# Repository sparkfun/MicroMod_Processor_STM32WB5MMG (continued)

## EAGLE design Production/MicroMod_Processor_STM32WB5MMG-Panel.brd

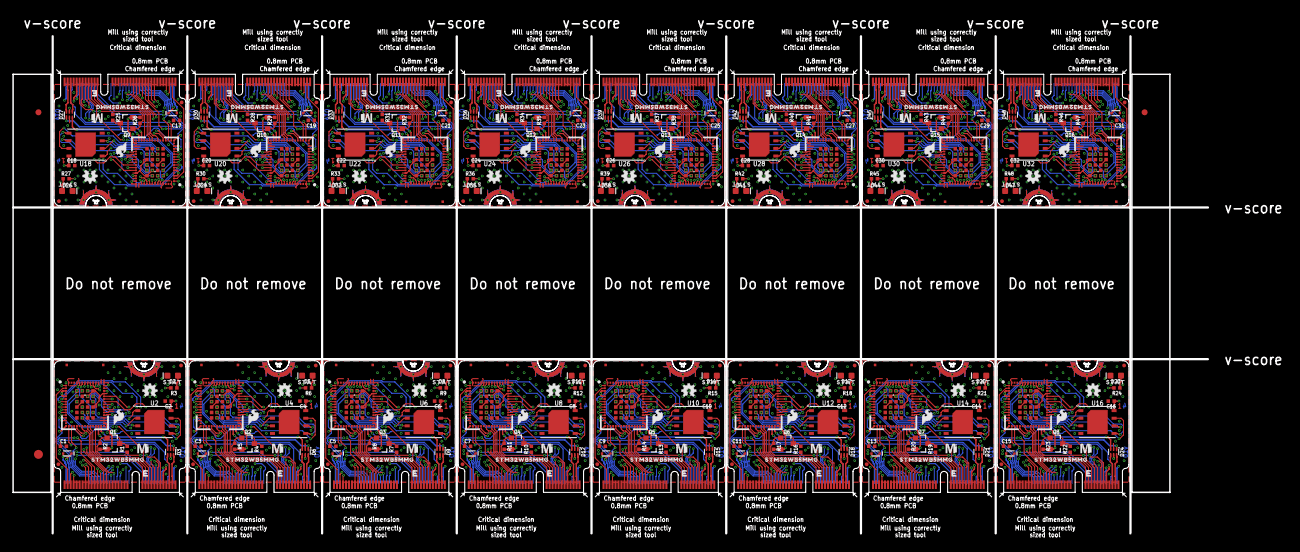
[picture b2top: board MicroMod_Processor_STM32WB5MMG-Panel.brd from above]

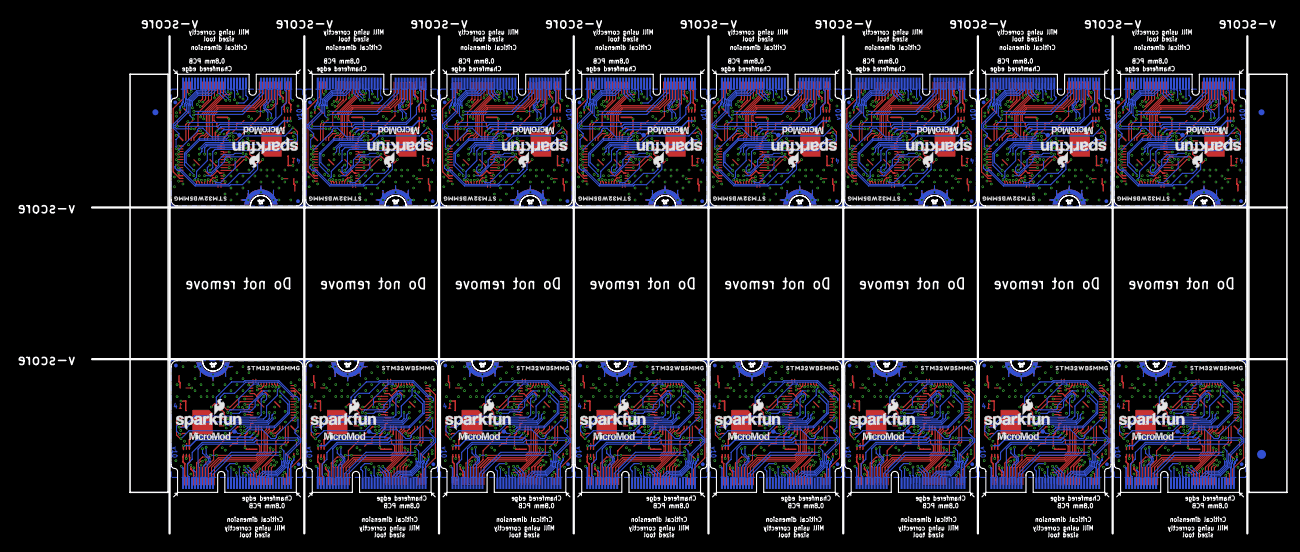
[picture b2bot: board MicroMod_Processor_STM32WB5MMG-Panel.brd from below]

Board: 4 copper layers, 199.6 x 83.1 mm, 438 parts (115 on the bottom side), 896 nets.

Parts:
C1, C2, C3, C4, C5, C6, C7, C8, C9, C10, C11, C12, C13, C14, C15, C16, C17, C18, C19, C20, C21, C22, C23, C24, C25, C26, C27, C28, C29, C30, C31, C32: 0.1uF; 0402-TIGHT
D1, D4, D7, D10, D13, D16, D19, D22, D25, D28, D31, D34, D37, D40, D43, D46: 120mA/40V/370mV; SOD-523
D2, D5, D8, D11, D14, D17, D20, D23, D26, D29, D32, D35, D38, D41, D44, D47: BLUE; LED-0603
D3, D6, D9, D12, D15, D18, D21, D24, D27, D30, D33, D36, D39, D42, D45, D48: PRTR5V0U2F; SOT886
E$1, E$2, E$3, E$4: FIDUCIAL-1X2
E$5, E$6: FIDUCIAL-1.5X3
FD1, FD2, FD3, FD4, FD5, FD6, FD7, FD8, FD9, FD10, FD11, FD12, FD13, FD14, FD15, FD16, FD17, FD18, FD19, FD20, FD21, FD22, FD23, FD24, FD25, FD26, FD27, FD28, FD29, FD30, FD31, FD32, FD33, FD34, FD35, FD36, FD37, FD38, FD39, FD40, FD41, FD42, FD43, FD44, FD45, FD46, FD47, FD48, FD49, FD50, FD51, FD52, FD53, FD54, FD55, FD56, FD57, FD58, FD59, FD60, FD61, FD62, FD63, FD64: FIDUCIALUFIDUCIAL; FIDUCIAL-MICRO
J1, J2, J3, J4, J5, J6, J7, J8, J9, J10, J11, J12, J13, J14, J15, J16: MICROMOD-2222; M.2-CARD-E-22
LOGO1, LOGO4, LOGO7, LOGO10, LOGO13, LOGO16, LOGO19, LOGO22, LOGO25, LOGO28, LOGO31, LOGO34, LOGO37, LOGO40, LOGO43, LOGO46: FOUR_LAYER_WARNING
LOGO2, LOGO5, LOGO8, LOGO11, LOGO14, LOGO17, LOGO20, LOGO23, LOGO26, LOGO29, LOGO32, LOGO35, LOGO38, LOGO41, LOGO44, LOGO47: OSHW-LOGOMINI; OSHW-LOGO-MINI
LOGO3, LOGO6, LOGO9, LOGO12, LOGO15, LOGO18, LOGO21, LOGO24, LOGO27, LOGO30, LOGO33, LOGO36, LOGO39, LOGO42, LOGO45, LOGO48: SFE_LOGO_NAME_FLAME.1_INCH; SFE_LOGO_NAME_FLAME_.1
Q1, Q2, Q3, Q4, Q5, Q6, Q7, Q8, Q9, Q10, Q11, Q12, Q13, Q14, Q15, Q16: 20V/4.2A/52mΩ/1.4W; SOT23-3
R1, R2, R4, R5, R7, R8, R10, R11, R13, R14, R16, R17, R19, R20, R22, R23, R25, R26, R28, R29, R31, R32, R34, R35, R37, R38, R40, R41, R43, R44, R46, R47: 100k; 0402-TIGHT
R3, R6, R9, R12, R15, R18, R21, R24, R27, R30, R33, R36, R39, R42, R45, R48: 2.2k; 0402-TIGHT
TP1, TP2, TP3, TP4, TP5, TP6, TP7, TP8, TP9, TP10, TP11, TP12, TP13, TP14, TP15, TP16: TEST-POINT3; PAD.03X.03
U1, U3, U5, U7, U9, U11, U13, U15, U17, U19, U21, U23, U25, U27, U29, U31: STM32WB5MMG; SIP-LGA86
U2, U4, U6, U8, U10, U12, U14, U16, U18, U20, U22, U24, U26, U28, U30, U32: W25QXX128MBIT-6X5; WSON-8-6X5
U$1, U$8, U$15, U$22, U$29, U$36, U$43, U$50, U$57, U$64, U$71, U$78, U$85, U$92, U$99, U$106: MICROMOD_MI_LOGO_.35
U$2, U$9, U$16, U$23, U$30, U$37, U$44, U$51, U$58, U$65, U$72, U$79, U$86, U$93, U$100, U$107: MICROMOD_LOGO_.3
U$3, U$10, U$17, U$24, U$31, U$38, U$45, U$52, U$59, U$66, U$73, U$80, U$87, U$94, U$101, U$108: SFE_LOGO_FLAME_.1
U$4, U$5, U$11, U$12, U$18, U$19, U$25, U$26, U$32, U$33, U$39, U$40, U$46, U$47, U$53, U$54, U$60, U$61, U$67, U$68, U$74, U$75, U$81, U$82, U$88, U$89, U$95, U$96, U$102, U$103, U$109, U$110: STM32WB5MMG0
U$6, U$13, U$20, U$27, U$34, U$41, U$48, U$55, U$62, U$69, U$76, U$83, U$90, U$97, U$104, U$111: SFE_LOGO_FLAME_STOP_.1
U$7, U$14, U$21, U$28, U$35, U$42, U$49, U$56, U$63, U$70, U$77, U$84, U$91, U$98, U$105, U$112: STAT0

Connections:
3.3V: C2.1, D1.A, J1.2, J1.74, Q1.2, R2.2, U1.4, U1.6, U1.17, U1.32, U2.8
3.3V1: C4.1, D4.A, J2.2, J2.74, Q2.2, R5.2, U3.4, U3.6, U3.17, U3.32, U4.8
3.3V2: C6.1, D7.A, J3.2, J3.74, Q3.2, R8.2, U5.4, U5.6, U5.17, U5.32, U6.8
3.3V3: C8.1, D10.A, J4.2, J4.74, Q4.2, R11.2, U7.4, U7.6, U7.17, U7.32, U8.8
3.3V4: C10.1, D13.A, J5.2, J5.74, Q5.2, R14.2, U9.4, U9.6, U9.17, U9.32, U10.8
3.3V5: C12.1, D16.A, J6.2, J6.74, Q6.2, R17.2, U11.4, U11.6, U11.17, U11.32, U12.8
3.3V6: C14.1, D19.A, J7.2, J7.74, Q7.2, R20.2, U13.4, U13.6, U13.17, U13.32, U14.8
3.3V7: C16.1, D22.A, J8.2, J8.74, Q8.2, R23.2, U15.4, U15.6, U15.17, U15.32, U16.8
3.3V8: C18.1, D25.A, J9.2, J9.74, Q9.2, R26.2, U17.4, U17.6, U17.17, U17.32, U18.8
3.3V9: C20.1, D28.A, J10.2, J10.74, Q10.2, R29.2, U19.4, U19.6, U19.17, U19.32, U20.8
3.3V10: C22.1, D31.A, J11.2, J11.74, Q11.2, R32.2, U21.4, U21.6, U21.17, U21.32, U22.8
3.3V11: C24.1, D34.A, J12.2, J12.74, Q12.2, R35.2, U23.4, U23.6, U23.17, U23.32, U24.8
3.3V12: C26.1, D37.A, J13.2, J13.74, Q13.2, R38.2, U25.4, U25.6, U25.17, U25.32, U26.8
3.3V13: C28.1, D40.A, J14.2, J14.74, Q14.2, R41.2, U27.4, U27.6, U27.17, U27.32, U28.8
3.3V14: C30.1, D43.A, J15.2, J15.74, Q15.2, R44.2, U29.4, U29.6, U29.17, U29.32, U30.8
3.3V15: C32.1, D46.A, J16.2, J16.74, Q16.2, R47.2, U31.4, U31.6, U31.17, U31.32, U32.8
!BOOT!: J1.11, Q1.1, R2.1
!BOOT!1: J2.11, Q2.1, R5.1
!BOOT!2: J3.11, Q3.1, R8.1
!BOOT!3: J4.11, Q4.1, R11.1
!BOOT!4: J5.11, Q5.1, R14.1
!BOOT!5: J6.11, Q6.1, R17.1
!BOOT!6: J7.11, Q7.1, R20.1
!BOOT!7: J8.11, Q8.1, R23.1
!BOOT!8: J9.11, Q9.1, R26.1
!BOOT!9: J10.11, Q10.1, R29.1
!BOOT!10: J11.11, Q11.1, R32.1
!BOOT!11: J12.11, Q12.1, R35.1
!BOOT!12: J13.11, Q13.1, R38.1
!BOOT!13: J14.11, Q14.1, R41.1
!BOOT!14: J15.11, Q15.1, R44.1
!BOOT!15: J16.11, Q16.1, R47.1
!RESET!: C1.1, J1.6, U1.10
!RESET!1: C3.1, J2.6, U3.10
!RESET!2: C5.1, J3.6, U5.10
!RESET!3: C7.1, J4.6, U7.10
!RESET!4: C9.1, J5.6, U9.10
!RESET!5: C11.1, J6.6, U11.10
!RESET!6: C13.1, J7.6, U13.10
!RESET!7: C15.1, J8.6, U15.10
!RESET!8: C17.1, J9.6, U17.10
!RESET!9: C19.1, J10.6, U19.10
!RESET!10: C21.1, J11.6, U21.10
!RESET!11: C23.1, J12.6, U23.10
!RESET!12: C25.1, J13.6, U25.10
!RESET!13: C27.1, J14.6, U27.10
!RESET!14: C29.1, J15.6, U29.10
!RESET!15: C31.1, J16.6, U31.10
A0: J1.34, U1.8
A1: J1.38, U1.7
A2: J2.34, U3.8
A3: J2.38, U3.7
A4: J3.34, U5.8
A5: J3.38, U5.7
A6: J4.34, U7.8
A7: J4.38, U7.7
A8: J5.34, U9.8
A9: J5.38, U9.7
A10: J6.34, U11.8
A11: J6.38, U11.7
A12: J7.34, U13.8
A13: J7.38, U13.7
A14: J8.34, U15.8
A15: J8.38, U15.7
A16: J9.34, U17.8
A17: J9.38, U17.7
A18: J10.34, U19.8
A19: J10.38, U19.7
A20: J11.34, U21.8
A21: J11.38, U21.7
A22: J12.34, U23.8
A23: J12.38, U23.7
A24: J13.34, U25.8
A25: J13.38, U25.7
A26: J14.34, U27.8
A27: J14.38, U27.7
A28: J15.34, U29.8
A29: J15.38, U29.7
A30: J16.34, U31.8
A31: J16.38, U31.7
AUD_BCLK: J1.50, U1.50
AUD_BCLK1: J2.50, U3.50
AUD_BCLK2: J3.50, U5.50
AUD_BCLK3: J4.50, U7.50
AUD_BCLK4: J5.50, U9.50
AUD_BCLK5: J6.50, U11.50
AUD_BCLK6: J7.50, U13.50
AUD_BCLK7: J8.50, U15.50
AUD_BCLK8: J9.50, U17.50
AUD_BCLK9: J10.50, U19.50
AUD_BCLK10: J11.50, U21.50
AUD_BCLK11: J12.50, U23.50
AUD_BCLK12: J13.50, U25.50
AUD_BCLK13: J14.50, U27.50
AUD_BCLK14: J15.50, U29.50
AUD_BCLK15: J16.50, U31.50
AUD_FSYNC: J1.52, U1.11
AUD_FSYNC1: J2.52, U3.11
AUD_FSYNC2: J3.52, U5.11
AUD_FSYNC3: J4.52, U7.11
AUD_FSYNC4: J5.52, U9.11
AUD_FSYNC5: J6.52, U11.11
AUD_FSYNC6: J7.52, U13.11
AUD_FSYNC7: J8.52, U15.11
AUD_FSYNC8: J9.52, U17.11
AUD_FSYNC9: J10.52, U19.11
AUD_FSYNC10: J11.52, U21.11
AUD_FSYNC11: J12.52, U23.11
AUD_FSYNC12: J13.52, U25.11
AUD_FSYNC13: J14.52, U27.11
AUD_FSYNC14: J15.52, U29.11
AUD_FSYNC15: J16.52, U31.11
AUD_I2S_IN: J1.54, U1.19
AUD_I2S_IN1: J2.54, U3.19
AUD_I2S_IN2: J3.54, U5.19
AUD_I2S_IN3: J4.54, U7.19
AUD_I2S_IN4: J5.54, U9.19
AUD_I2S_IN5: J6.54, U11.19
AUD_I2S_IN6: J7.54, U13.19
AUD_I2S_IN7: J8.54, U15.19
AUD_I2S_IN8: J9.54, U17.19
AUD_I2S_IN9: J10.54, U19.19
AUD_I2S_IN10: J11.54, U21.19
AUD_I2S_IN11: J12.54, U23.19
AUD_I2S_IN12: J13.54, U25.19
AUD_I2S_IN13: J14.54, U27.19
AUD_I2S_IN14: J15.54, U29.19
AUD_I2S_IN15: J16.54, U31.19
AUD_I2S_OUT: J1.56, U1.38
AUD_I2S_OUT1: J2.56, U3.38
AUD_I2S_OUT2: J3.56, U5.38
AUD_I2S_OUT3: J4.56, U7.38
AUD_I2S_OUT4: J5.56, U9.38
AUD_I2S_OUT5: J6.56, U11.38
AUD_I2S_OUT6: J7.56, U13.38
AUD_I2S_OUT7: J8.56, U15.38
AUD_I2S_OUT8: J9.56, U17.38
AUD_I2S_OUT9: J10.56, U19.38
AUD_I2S_OUT10: J11.56, U21.38
AUD_I2S_OUT11: J12.56, U23.38
AUD_I2S_OUT12: J13.56, U25.38
AUD_I2S_OUT13: J14.56, U27.38
AUD_I2S_OUT14: J15.56, U29.38
AUD_I2S_OUT15: J16.56, U31.38
AUD_MCLK: J1.58, U1.14
AUD_MCLK1: J2.58, U3.14
AUD_MCLK2: J3.58, U5.14
AUD_MCLK3: J4.58, U7.14
AUD_MCLK4: J5.58, U9.14
AUD_MCLK5: J6.58, U11.14
AUD_MCLK6: J7.58, U13.14
AUD_MCLK7: J8.58, U15.14
AUD_MCLK8: J9.58, U17.14
AUD_MCLK9: J10.58, U19.14
AUD_MCLK10: J11.58, U21.14
AUD_MCLK11: J12.58, U23.14
AUD_MCLK12: J13.58, U25.14
AUD_MCLK13: J14.58, U27.14
AUD_MCLK14: J15.58, U29.14
AUD_MCLK15: J16.58, U31.14
BATT_VIN: J1.49, U1.49
BATT_VIN1: J2.49, U3.49
BATT_VIN2: J3.49, U5.49
BATT_VIN3: J4.49, U7.49
BATT_VIN4: J5.49, U9.49
BATT_VIN5: J6.49, U11.49
BATT_VIN6: J7.49, U13.49
BATT_VIN7: J8.49, U15.49
BATT_VIN8: J9.49, U17.49
BATT_VIN9: J10.49, U19.49
BATT_VIN10: J11.49, U21.49
BATT_VIN11: J12.49, U23.49
BATT_VIN12: J13.49, U25.49
BATT_VIN13: J14.49, U27.49
BATT_VIN14: J15.49, U29.49
BATT_VIN15: J16.49, U31.49
BOOT0: Q1.3, R1.2, TP1.1, U1.13
BOOT1: Q2.3, R4.2, TP2.1, U3.13
BOOT2: Q3.3, R7.2, TP3.1, U5.13
BOOT3: Q4.3, R10.2, TP4.1, U7.13
BOOT4: Q5.3, R13.2, TP5.1, U9.13
BOOT5: Q6.3, R16.2, TP6.1, U11.13
BOOT6: Q7.3, R19.2, TP7.1, U13.13
BOOT7: Q8.3, R22.2, TP8.1, U15.13
BOOT8: Q9.3, R25.2, TP9.1, U17.13
BOOT9: Q10.3, R28.2, TP10.1, U19.13
BOOT10: Q11.3, R31.2, TP11.1, U21.13
BOOT11: Q12.3, R34.2, TP12.1, U23.13
BOOT12: Q13.3, R37.2, TP13.1, U25.13
BOOT13: Q14.3, R40.2, TP14.1, U27.13
BOOT14: Q15.3, R43.2, TP15.1, U29.13
BOOT15: Q16.3, R46.2, TP16.1, U31.13
GND: C1.2, C2.2, D2.C, D3.2, J1.1, J1.7, J1.33, J1.36, J1.39, J1.45, J1.75, J1.GND1, J1.GND2, J1.GND3, R1.1, U1.5, U1.16, U1.22, U1.24, U1.27, U1.31, U1.33, U1.34, U1.36, U1.43, U1.44, U1.45, U1.46, U1.47, U1.48, U1.57, U1.58, U1.59, U1.60, U1.64, U1.65, U1.66, U1.68, U1.69, U1.71, U1.74, U1.77, U1.78, U1.82, U1.83, U1.84, U1.86, U2.4
GND2: C3.2, C4.2, D5.C, D6.2, J2.1, J2.7, J2.33, J2.36, J2.39, J2.45, J2.75, J2.GND1, J2.GND2, J2.GND3, R4.1, U3.5, U3.16, U3.22, U3.24, U3.27, U3.31, U3.33, U3.34, U3.36, U3.43, U3.44, U3.45, U3.46, U3.47, U3.48, U3.57, U3.58, U3.59, U3.60, U3.64, U3.65, U3.66, U3.68, U3.69, U3.71, U3.74, U3.77, U3.78, U3.82, U3.83, U3.84, U3.86, U4.4
GND4: C5.2, C6.2, D8.C, D9.2, J3.1, J3.7, J3.33, J3.36, J3.39, J3.45, J3.75, J3.GND1, J3.GND2, J3.GND3, R7.1, U5.5, U5.16, U5.22, U5.24, U5.27, U5.31, U5.33, U5.34, U5.36, U5.43, U5.44, U5.45, U5.46, U5.47, U5.48, U5.57, U5.58, U5.59, U5.60, U5.64, U5.65, U5.66, U5.68, U5.69, U5.71, U5.74, U5.77, U5.78, U5.82, U5.83, U5.84, U5.86, U6.4
GND6: C7.2, C8.2, D11.C, D12.2, J4.1, J4.7, J4.33, J4.36, J4.39, J4.45, J4.75, J4.GND1, J4.GND2, J4.GND3, R10.1, U7.5, U7.16, U7.22, U7.24, U7.27, U7.31, U7.33, U7.34, U7.36, U7.43, U7.44, U7.45, U7.46, U7.47, U7.48, U7.57, U7.58, U7.59, U7.60, U7.64, U7.65, U7.66, U7.68, U7.69, U7.71, U7.74, U7.77, U7.78, U7.82, U7.83, U7.84, U7.86, U8.4
GND8: C9.2, C10.2, D14.C, D15.2, J5.1, J5.7, J5.33, J5.36, J5.39, J5.45, J5.75, J5.GND1, J5.GND2, J5.GND3, R13.1, U9.5, U9.16, U9.22, U9.24, U9.27, U9.31, U9.33, U9.34, U9.36, U9.43, U9.44, U9.45, U9.46, U9.47, U9.48, U9.57, U9.58, U9.59, U9.60, U9.64, U9.65, U9.66, U9.68, U9.69, U9.71, U9.74, U9.77, U9.78, U9.82, U9.83, U9.84, U9.86, U10.4
GND10: C11.2, C12.2, D17.C, D18.2, J6.1, J6.7, J6.33, J6.36, J6.39, J6.45, J6.75, J6.GND1, J6.GND2, J6.GND3, R16.1, U11.5, U11.16, U11.22, U11.24, U11.27, U11.31, U11.33, U11.34, U11.36, U11.43, U11.44, U11.45, U11.46, U11.47, U11.48, U11.57, U11.58, U11.59, U11.60, U11.64, U11.65, U11.66, U11.68, U11.69, U11.71, U11.74, U11.77, U11.78, U11.82, U11.83, U11.84, U11.86, U12.4
GND12: C13.2, C14.2, D20.C, D21.2, J7.1, J7.7, J7.33, J7.36, J7.39, J7.45, J7.75, J7.GND1, J7.GND2, J7.GND3, R19.1, U13.5, U13.16, U13.22, U13.24, U13.27, U13.31, U13.33, U13.34, U13.36, U13.43, U13.44, U13.45, U13.46, U13.47, U13.48, U13.57, U13.58, U13.59, U13.60, U13.64, U13.65, U13.66, U13.68, U13.69, U13.71, U13.74, U13.77, U13.78, U13.82, U13.83, U13.84, U13.86, U14.4
GND14: C15.2, C16.2, D23.C, D24.2, J8.1, J8.7, J8.33, J8.36, J8.39, J8.45, J8.75, J8.GND1, J8.GND2, J8.GND3, R22.1, U15.5, U15.16, U15.22, U15.24, U15.27, U15.31, U15.33, U15.34, U15.36, U15.43, U15.44, U15.45, U15.46, U15.47, U15.48, U15.57, U15.58, U15.59, U15.60, U15.64, U15.65, U15.66, U15.68, U15.69, U15.71, U15.74, U15.77, U15.78, U15.82, U15.83, U15.84, U15.86, U16.4
GND16: C17.2, C18.2, D26.C, D27.2, J9.1, J9.7, J9.33, J9.36, J9.39, J9.45, J9.75, J9.GND1, J9.GND2, J9.GND3, R25.1, U17.5, U17.16, U17.22, U17.24, U17.27, U17.31, U17.33, U17.34, U17.36, U17.43, U17.44, U17.45, U17.46, U17.47, U17.48, U17.57, U17.58, U17.59, U17.60, U17.64, U17.65, U17.66, U17.68, U17.69, U17.71, U17.74, U17.77, U17.78, U17.82, U17.83, U17.84, U17.86, U18.4
GND18: C19.2, C20.2, D29.C, D30.2, J10.1, J10.7, J10.33, J10.36, J10.39, J10.45, J10.75, J10.GND1, J10.GND2, J10.GND3, R28.1, U19.5, U19.16, U19.22, U19.24, U19.27, U19.31, U19.33, U19.34, U19.36, U19.43, U19.44, U19.45, U19.46, U19.47, U19.48, U19.57, U19.58, U19.59, U19.60, U19.64, U19.65, U19.66, U19.68, U19.69, U19.71, U19.74, U19.77, U19.78, U19.82, U19.83, U19.84, U19.86, U20.4
GND20: C21.2, C22.2, D32.C, D33.2, J11.1, J11.7, J11.33, J11.36, J11.39, J11.45, J11.75, J11.GND1, J11.GND2, J11.GND3, R31.1, U21.5, U21.16, U21.22, U21.24, U21.27, U21.31, U21.33, U21.34, U21.36, U21.43, U21.44, U21.45, U21.46, U21.47, U21.48, U21.57, U21.58, U21.59, U21.60, U21.64, U21.65, U21.66, U21.68, U21.69, U21.71, U21.74, U21.77, U21.78, U21.82, U21.83, U21.84, U21.86, U22.4
GND22: C23.2, C24.2, D35.C, D36.2, J12.1, J12.7, J12.33, J12.36, J12.39, J12.45, J12.75, J12.GND1, J12.GND2, J12.GND3, R34.1, U23.5, U23.16, U23.22, U23.24, U23.27, U23.31, U23.33, U23.34, U23.36, U23.43, U23.44, U23.45, U23.46, U23.47, U23.48, U23.57, U23.58, U23.59, U23.60, U23.64, U23.65, U23.66, U23.68, U23.69, U23.71, U23.74, U23.77, U23.78, U23.82, U23.83, U23.84, U23.86, U24.4
GND24: C25.2, C26.2, D38.C, D39.2, J13.1, J13.7, J13.33, J13.36, J13.39, J13.45, J13.75, J13.GND1, J13.GND2, J13.GND3, R37.1, U25.5, U25.16, U25.22, U25.24, U25.27, U25.31, U25.33, U25.34, U25.36, U25.43, U25.44, U25.45, U25.46, U25.47, U25.48, U25.57, U25.58, U25.59, U25.60, U25.64, U25.65, U25.66, U25.68, U25.69, U25.71, U25.74, U25.77, U25.78, U25.82, U25.83, U25.84, U25.86, U26.4
GND26: C27.2, C28.2, D41.C, D42.2, J14.1, J14.7, J14.33, J14.36, J14.39, J14.45, J14.75, J14.GND1, J14.GND2, J14.GND3, R40.1, U27.5, U27.16, U27.22, U27.24, U27.27, U27.31, U27.33, U27.34, U27.36, U27.43, U27.44, U27.45, U27.46, U27.47, U27.48, U27.57, U27.58, U27.59, U27.60, U27.64, U27.65, U27.66, U27.68, U27.69, U27.71, U27.74, U27.77, U27.78, U27.82, U27.83, U27.84, U27.86, U28.4
GND28: C29.2, C30.2, D44.C, D45.2, J15.1, J15.7, J15.33, J15.36, J15.39, J15.45, J15.75, J15.GND1, J15.GND2, J15.GND3, R43.1, U29.5, U29.16, U29.22, U29.24, U29.27, U29.31, U29.33, U29.34, U29.36, U29.43, U29.44, U29.45, U29.46, U29.47, U29.48, U29.57, U29.58, U29.59, U29.60, U29.64, U29.65, U29.66, U29.68, U29.69, U29.71, U29.74, U29.77, U29.78, U29.82, U29.83, U29.84, U29.86, U30.4
GND30: C31.2, C32.2, D47.C, D48.2, J16.1, J16.7, J16.33, J16.36, J16.39, J16.45, J16.75, J16.GND1, J16.GND2, J16.GND3, R46.1, U31.5, U31.16, U31.22, U31.24, U31.27, U31.31, U31.33, U31.34, U31.36, U31.43, U31.44, U31.45, U31.46, U31.47, U31.48, U31.57, U31.58, U31.59, U31.60, U31.64, U31.65, U31.66, U31.68, U31.69, U31.71, U31.74, U31.77, U31.78, U31.82, U31.83, U31.84, U31.86, U32.4
I2C1_INT: J1.16, U1.2
I2C1_INT1: J2.16, U3.2
I2C1_INT2: J3.16, U5.2
I2C1_INT3: J4.16, U7.2
I2C1_INT4: J5.16, U9.2
I2C1_INT5: J6.16, U11.2
I2C1_INT6: J7.16, U13.2
I2C1_INT7: J8.16, U15.2
I2C1_INT8: J9.16, U17.2
I2C1_INT9: J10.16, U19.2
I2C1_INT10: J11.16, U21.2
I2C1_INT11: J12.16, U23.2
I2C1_INT12: J13.16, U25.2
I2C1_INT13: J14.16, U27.2
I2C1_INT14: J15.16, U29.2
I2C1_INT15: J16.16, U31.2
I2C1_SCL: J1.14, U1.39
I2C1_SCL1: J2.14, U3.39
I2C1_SCL2: J3.14, U5.39
I2C1_SCL3: J4.14, U7.39
I2C1_SCL4: J5.14, U9.39
I2C1_SCL5: J6.14, U11.39
I2C1_SCL6: J7.14, U13.39
I2C1_SCL7: J8.14, U15.39
I2C1_SCL8: J9.14, U17.39
I2C1_SCL9: J10.14, U19.39
I2C1_SCL10: J11.14, U21.39
I2C1_SCL11: J12.14, U23.39
I2C1_SCL12: J13.14, U25.39
I2C1_SCL13: J14.14, U27.39
I2C1_SCL14: J15.14, U29.39
I2C1_SCL15: J16.14, U31.39
I2C1_SDA: J1.12, U1.18
I2C1_SDA1: J2.12, U3.18
I2C1_SDA2: J3.12, U5.18
I2C1_SDA3: J4.12, U7.18
I2C1_SDA4: J5.12, U9.18
I2C1_SDA5: J6.12, U11.18
I2C1_SDA6: J7.12, U13.18
I2C1_SDA7: J8.12, U15.18
I2C1_SDA8: J9.12, U17.18
I2C1_SDA9: J10.12, U19.18
I2C1_SDA10: J11.12, U21.18
I2C1_SDA11: J12.12, U23.18
I2C1_SDA12: J13.12, U25.18
I2C1_SDA13: J14.12, U27.18
I2C1_SDA14: J15.12, U29.18
I2C1_SDA15: J16.12, U31.18
I2C3_SCL1: J1.53, U1.35
I2C3_SCL2: J2.53, U3.35
I2C3_SCL3: J3.53, U5.35
I2C3_SCL4: J4.53, U7.35
I2C3_SCL5: J5.53, U9.35
I2C3_SCL6: J6.53, U11.35
I2C3_SCL7: J7.53, U13.35
I2C3_SCL8: J8.53, U15.35
I2C3_SCL9: J9.53, U17.35
I2C3_SCL10: J10.53, U19.35
I2C3_SCL11: J11.53, U21.35
I2C3_SCL12: J12.53, U23.35
I2C3_SCL13: J13.53, U25.35
I2C3_SCL14: J14.53, U27.35
I2C3_SCL15: J15.53, U29.35
I2C3_SCL16: J16.53, U31.35
I2C3_SDA1: J1.51, U1.37
I2C3_SDA2: J2.51, U3.37
I2C3_SDA3: J3.51, U5.37
I2C3_SDA4: J4.51, U7.37
I2C3_SDA5: J5.51, U9.37
I2C3_SDA6: J6.51, U11.37
I2C3_SDA7: J7.51, U13.37
I2C3_SDA8: J8.51, U15.37
I2C3_SDA9: J9.51, U17.37
I2C3_SDA10: J10.51, U19.37
I2C3_SDA11: J11.51, U21.37
I2C3_SDA12: J12.51, U23.37
I2C3_SDA13: J13.51, U25.37
I2C3_SDA14: J14.51, U27.37
I2C3_SDA15: J15.51, U29.37
I2C3_SDA16: J16.51, U31.37
LP_RX2/DEV_TX1: J2.20, U3.12
LP_RX2/DEV_TX2: J1.20, U1.12
LP_RX2/DEV_TX3: J3.20, U5.12
LP_RX2/DEV_TX4: J4.20, U7.12
LP_RX2/DEV_TX5: J5.20, U9.12
LP_RX2/DEV_TX6: J6.20, U11.12
LP_RX2/DEV_TX7: J7.20, U13.12
LP_RX2/DEV_TX8: J8.20, U15.12
LP_RX2/DEV_TX9: J9.20, U17.12
LP_RX2/DEV_TX10: J10.20, U19.12
LP_RX2/DEV_TX11: J11.20, U21.12
LP_RX2/DEV_TX12: J12.20, U23.12
LP_RX2/DEV_TX13: J13.20, U25.12
LP_RX2/DEV_TX14: J14.20, U27.12
LP_RX2/DEV_TX15: J15.20, U29.12
LP_RX2/DEV_TX16: J16.20, U31.12
LP_TX2/DEV_RX1: J2.22, U3.9
LP_TX2/DEV_RX2: J1.22, U1.9
LP_TX2/DEV_RX3: J3.22, U5.9
LP_TX2/DEV_RX4: J4.22, U7.9
LP_TX2/DEV_RX5: J5.22, U9.9
LP_TX2/DEV_RX6: J6.22, U11.9
LP_TX2/DEV_RX7: J7.22, U13.9
LP_TX2/DEV_RX8: J8.22, U15.9
LP_TX2/DEV_RX9: J9.22, U17.9
LP_TX2/DEV_RX10: J10.22, U19.9
LP_TX2/DEV_RX11: J11.22, U21.9
LP_TX2/DEV_RX12: J12.22, U23.9
LP_TX2/DEV_RX13: J13.22, U25.9
LP_TX2/DEV_RX14: J14.22, U27.9
LP_TX2/DEV_RX15: J15.22, U29.9
LP_TX2/DEV_RX16: J16.22, U31.9
unnamed: D2.A, R3.1
unnamed: D5.A, R6.1
unnamed: D6.5, J2.9
unnamed: D3.5, J1.9
unnamed: D8.A, R9.1
unnamed: D9.5, J3.9
unnamed: D11.A, R12.1
unnamed: D12.5, J4.9
unnamed: D14.A, R15.1
unnamed: D15.5, J5.9
unnamed: D17.A, R18.1
unnamed: D18.5, J6.9
unnamed: D20.A, R21.1
unnamed: D21.5, J7.9
unnamed: D23.A, R24.1
unnamed: D24.5, J8.9
unnamed: D26.A, R27.1
unnamed: D27.5, J9.9
unnamed: D29.A, R30.1
unnamed: D30.5, J10.9
unnamed: D32.A, R33.1
unnamed: D33.5, J11.9
unnamed: D35.A, R36.1
unnamed: D36.5, J12.9
unnamed: D38.A, R39.1
unnamed: D39.5, J13.9
unnamed: D41.A, R42.1
unnamed: D42.5, J14.9
unnamed: D44.A, R45.1
unnamed: D45.5, J15.9
unnamed: D47.A, R48.1
unnamed: D48.5, J16.9
PA0/G1: J2.73, U3.3
PA0/G2: J3.73, U5.3
PA0/G3: J4.73, U7.3
PA0/G4: J5.73, U9.3
PA0/G5: J1.73, U1.3
PA0/G6: J6.73, U11.3
PA0/G7: J7.73, U13.3
PA0/G8: J8.73, U15.3
PA0/G9: J9.73, U17.3
PA0/G10: J10.73, U19.3
PA0/G11: J11.73, U21.3
PA0/G12: J12.73, U23.3
PA0/G13: J13.73, U25.3
PA0/G14: J14.73, U27.3
PA0/G15: J15.73, U29.3
PA0/G16: J16.73, U31.3
PC11/G1: J1.42, U1.23
PC11/G2: J2.42, U3.23
PC11/G3: J3.42, U5.23
PC11/G4: J4.42, U7.23
PC11/G5: J5.42, U9.23
PC11/G6: J6.42, U11.23
PC11/G7: J7.42, U13.23
PC11/G8: J8.42, U15.23
PC11/G9: J9.42, U17.23
PC11/G10: J10.42, U19.23
PC11/G11: J11.42, U21.23
PC11/G12: J12.42, U23.23
PC11/G13: J13.42, U25.23
PC11/G14: J14.42, U27.23
PC11/G15: J15.42, U29.23
PC11/G16: J16.42, U31.23
PC13/G1: J2.44, U3.40
PC13/G2: J1.44, U1.40
PC13/G3: J3.44, U5.40
PC13/G4: J4.44, U7.40
PC13/G5: J5.44, U9.40
PC13/G6: J6.44, U11.40
PC13/G7: J7.44, U13.40
PC13/G8: J8.44, U15.40
PC13/G9: J9.44, U17.40
PC13/G10: J10.44, U19.40
PC13/G11: J11.44, U21.40
PC13/G12: J12.44, U23.40
PC13/G13: J13.44, U25.40
PC13/G14: J14.44, U27.40
PC13/G15: J15.44, U29.40
PC13/G16: J16.44, U31.40
PD8/G1: J2.46, U3.75
PD8/G2: J3.46, U5.75
PD8/G3: J1.46, U1.75
PD8/G4: J4.46, U7.75
PD8/G5: J5.46, U9.75
PD8/G6: J6.46, U11.75
PD8/G7: J7.46, U13.75
PD8/G8: J8.46, U15.75
PD8/G9: J9.46, U17.75
PD8/G10: J10.46, U19.75
PD8/G11: J11.46, U21.75
PD8/G12: J12.46, U23.75
PD8/G13: J13.46, U25.75
PD8/G14: J14.46, U27.75
PD8/G15: J15.46, U29.75
PD8/G16: J16.46, U31.75
PE3/G1: J2.48, U3.72
PE3/G2: J3.48, U5.72
PE3/G3: J4.48, U7.72
PE3/G4: J1.48, U1.72
PE3/G5: J5.48, U9.72
PE3/G6: J6.48, U11.72
PE3/G7: J7.48, U13.72
PE3/G8: J8.48, U15.72
PE3/G9: J9.48, U17.72
PE3/G10: J10.48, U19.72
PE3/G11: J11.48, U21.72
PE3/G12: J12.48, U23.72
PE3/G13: J13.48, U25.72
PE3/G14: J14.48, U27.72
PE3/G15: J15.48, U29.72
PE3/G16: J16.48, U31.72
PE4/G0: J1.40, U1.42
PE4/G1: J2.40, U3.42
PE4/G2: J3.40, U5.42
PE4/G3: J4.40, U7.42
PE4/G4: J5.40, U9.42
PE4/G5: J6.40, U11.42
PE4/G6: J7.40, U13.42
PE4/G7: J8.40, U15.42
PE4/G8: J9.40, U17.42
PE4/G9: J10.40, U19.42
PE4/G10: J11.40, U21.42
PE4/G11: J12.40, U23.42
PE4/G12: J13.40, U25.42
PE4/G13: J14.40, U27.42
PE4/G14: J15.40, U29.42
PE4/G15: J16.40, U31.42
PH0/G1: J2.69, U3.61
PH0/G2: J3.69, U5.61
PH0/G3: J4.69, U7.61
PH0/G4: J5.69, U9.61
PH0/G5: J6.69, U11.61
PH0/G6: J7.69, U13.61
PH0/G7: J1.69, U1.61
PH0/G8: J8.69, U15.61
PH0/G9: J9.69, U17.61
PH0/G10: J10.69, U19.61
PH0/G11: J11.69, U21.61
PH0/G12: J12.69, U23.61
PH0/G13: J13.69, U25.61
PH0/G14: J14.69, U27.61
PH0/G15: J15.69, U29.61
PH0/G16: J16.69, U31.61
PH1/G1: J2.71, U3.62
PH1/G2: J3.71, U5.62
PH1/G3: J4.71, U7.62
PH1/G4: J5.71, U9.62
PH1/G5: J6.71, U11.62
PH1/G6: J1.71, U1.62
PH1/G7: J7.71, U13.62
PH1/G8: J8.71, U15.62
PH1/G9: J9.71, U17.62
PH1/G10: J10.71, U19.62
PH1/G11: J11.71, U21.62
PH1/G12: J12.71, U23.62
PH1/G13: J13.71, U25.62
PH1/G14: J14.71, U27.62
PH1/G15: J15.71, U29.62
PH1/G16: J16.71, U31.62
PWM0: J1.32, U1.63
PWM1: J1.47, U1.76
PWM2: J2.32, U3.63
PWM3: J2.47, U3.76
PWM4: J3.32, U5.63
PWM5: J3.47, U5.76
PWM6: J4.32, U7.63
PWM7: J4.47, U7.76
PWM8: J5.32, U9.63
PWM9: J5.47, U9.76
PWM10: J6.32, U11.63
PWM11: J6.47, U11.76
PWM12: J7.32, U13.63
PWM13: J7.47, U13.76
PWM14: J8.32, U15.63
PWM15: J8.47, U15.76
PWM16: J9.32, U17.63
PWM17: J9.47, U17.76
PWM18: J10.32, U19.63
PWM19: J10.47, U19.76
PWM20: J11.32, U21.63
PWM21: J11.47, U21.76
PWM22: J12.32, U23.63
PWM23: J12.47, U23.76
PWM24: J13.32, U25.63
PWM25: J13.47, U25.76
PWM26: J14.32, U27.63
PWM27: J14.47, U27.76
PWM28: J15.32, U29.63
PWM29: J15.47, U29.76
PWM30: J16.32, U31.63
PWM31: J16.47, U31.76
QSPI_!CS!: U1.70, U2.1
QSPI_!CS!1: U3.70, U4.1
QSPI_!CS!2: U5.70, U6.1
QSPI_!CS!3: U7.70, U8.1
QSPI_!CS!4: U9.70, U10.1
QSPI_!CS!5: U11.70, U12.1
QSPI_!CS!6: U13.70, U14.1
QSPI_!CS!7: U15.70, U16.1
QSPI_!CS!8: U17.70, U18.1
QSPI_!CS!9: U19.70, U20.1
QSPI_!CS!10: U21.70, U22.1
QSPI_!CS!11: U23.70, U24.1
QSPI_!CS!12: U25.70, U26.1
QSPI_!CS!13: U27.70, U28.1
QSPI_!CS!14: U29.70, U30.1
QSPI_!CS!15: U31.70, U32.1
QSPI_CLK: U1.56, U2.6
QSPI_CLK1: U3.56, U4.6
QSPI_CLK2: U5.56, U6.6
QSPI_CLK3: U7.56, U8.6
QSPI_CLK4: U9.56, U10.6
QSPI_CLK5: U11.56, U12.6
QSPI_CLK6: U13.56, U14.6
QSPI_CLK7: U15.56, U16.6
QSPI_CLK8: U17.56, U18.6
QSPI_CLK9: U19.56, U20.6
QSPI_CLK10: U21.56, U22.6
QSPI_CLK11: U23.56, U24.6
QSPI_CLK12: U25.56, U26.6
QSPI_CLK13: U27.56, U28.6
QSPI_CLK14: U29.56, U30.6
QSPI_CLK15: U31.56, U32.6
QSPI_IO0: U1.73, U2.5
QSPI_IO1: U1.80, U2.2
QSPI_IO2: U1.81, U2.3
QSPI_IO3: U1.67, U2.7
QSPI_IO4: U3.73, U4.5
QSPI_IO5: U3.80, U4.2
QSPI_IO6: U3.81, U4.3
QSPI_IO7: U3.67, U4.7
QSPI_IO8: U5.73, U6.5
QSPI_IO9: U5.80, U6.2
QSPI_IO10: U5.81, U6.3
QSPI_IO11: U5.67, U6.7
QSPI_IO12: U7.73, U8.5
QSPI_IO13: U7.80, U8.2
QSPI_IO14: U7.81, U8.3
QSPI_IO15: U7.67, U8.7
QSPI_IO16: U9.73, U10.5
QSPI_IO17: U9.80, U10.2
QSPI_IO18: U9.81, U10.3
QSPI_IO19: U9.67, U10.7
QSPI_IO20: U11.73, U12.5
QSPI_IO21: U11.80, U12.2
QSPI_IO22: U11.81, U12.3
QSPI_IO23: U11.67, U12.7
QSPI_IO24: U13.73, U14.5
QSPI_IO25: U13.80, U14.2
QSPI_IO26: U13.81, U14.3
QSPI_IO27: U13.67, U14.7
QSPI_IO28: U15.73, U16.5
QSPI_IO29: U15.80, U16.2
QSPI_IO30: U15.81, U16.3
QSPI_IO31: U15.67, U16.7
QSPI_IO32: U17.73, U18.5
QSPI_IO33: U17.80, U18.2
QSPI_IO34: U17.81, U18.3
QSPI_IO35: U17.67, U18.7
QSPI_IO36: U19.73, U20.5
QSPI_IO37: U19.80, U20.2
QSPI_IO38: U19.81, U20.3
QSPI_IO39: U19.67, U20.7
QSPI_IO40: U21.73, U22.5
QSPI_IO41: U21.80, U22.2
QSPI_IO42: U21.81, U22.3
QSPI_IO43: U21.67, U22.7
QSPI_IO44: U23.73, U24.5
QSPI_IO45: U23.80, U24.2
QSPI_IO46: U23.81, U24.3
QSPI_IO47: U23.67, U24.7
QSPI_IO48: U25.73, U26.5
QSPI_IO49: U25.80, U26.2
QSPI_IO50: U25.81, U26.3
QSPI_IO51: U25.67, U26.7
QSPI_IO52: U27.73, U28.5
QSPI_IO53: U27.80, U28.2
QSPI_IO54: U27.81, U28.3
QSPI_IO55: U27.67, U28.7
QSPI_IO56: U29.73, U30.5
QSPI_IO57: U29.80, U30.2
QSPI_IO58: U29.81, U30.3
QSPI_IO59: U29.67, U30.7
QSPI_IO60: U31.73, U32.5
QSPI_IO61: U31.80, U32.2
QSPI_IO62: U31.81, U32.3
QSPI_IO63: U31.67, U32.7
RX1/DEV_TX1: J1.19, U1.28
RX1/DEV_TX2: J2.19, U3.28
RX1/DEV_TX3: J3.19, U5.28
RX1/DEV_TX4: J4.19, U7.28
RX1/DEV_TX5: J5.19, U9.28
RX1/DEV_TX6: J6.19, U11.28
RX1/DEV_TX7: J7.19, U13.28
RX1/DEV_TX8: J8.19, U15.28
RX1/DEV_TX9: J9.19, U17.28
RX1/DEV_TX10: J10.19, U19.28
RX1/DEV_TX11: J11.19, U21.28
RX1/DEV_TX12: J12.19, U23.28
RX1/DEV_TX13: J13.19, U25.28
RX1/DEV_TX14: J14.19, U27.28
RX1/DEV_TX15: J15.19, U29.28
RX1/DEV_TX16: J16.19, U31.28
SPI_!CS!: J1.55, U1.55
SPI_!CS!1: J2.55, U3.55
SPI_!CS!2: J3.55, U5.55
SPI_!CS!3: J4.55, U7.55
SPI_!CS!4: J5.55, U9.55
SPI_!CS!5: J6.55, U11.55
SPI_!CS!6: J7.55, U13.55
SPI_!CS!7: J8.55, U15.55
SPI_!CS!8: J9.55, U17.55
SPI_!CS!9: J10.55, U19.55
SPI_!CS!10: J11.55, U21.55
SPI_!CS!11: J12.55, U23.55
SPI_!CS!12: J13.55, U25.55
SPI_!CS!13: J14.55, U27.55
SPI_!CS!14: J15.55, U29.55
SPI_!CS!15: J16.55, U31.55
SPI_PICO: J1.59, U1.52
SPI_PICO1: J2.59, U3.52
SPI_PICO2: J3.59, U5.52
SPI_PICO3: J4.59, U7.52
SPI_PICO4: J5.59, U9.52
SPI_PICO5: J6.59, U11.52
SPI_PICO6: J7.59, U13.52
SPI_PICO7: J8.59, U15.52
SPI_PICO8: J9.59, U17.52
SPI_PICO9: J10.59, U19.52
SPI_PICO10: J11.59, U21.52
SPI_PICO11: J12.59, U23.52
SPI_PICO12: J13.59, U25.52
SPI_PICO13: J14.59, U27.52
SPI_PICO14: J15.59, U29.52
SPI_PICO15: J16.59, U31.52
SPI_POCI: J1.61, U1.53
SPI_POCI1: J2.61, U3.53
SPI_POCI2: J3.61, U5.53
SPI_POCI3: J4.61, U7.53
SPI_POCI4: J5.61, U9.53
SPI_POCI5: J6.61, U11.53
SPI_POCI6: J7.61, U13.53
SPI_POCI7: J8.61, U15.53
SPI_POCI8: J9.61, U17.53
SPI_POCI9: J10.61, U19.53
SPI_POCI10: J11.61, U21.53
SPI_POCI11: J12.61, U23.53
SPI_POCI12: J13.61, U25.53
SPI_POCI13: J14.61, U27.53
SPI_POCI14: J15.61, U29.53
SPI_POCI15: J16.61, U31.53
SPI_SCK: J1.57, U1.54
SPI_SCK1: J2.57, U3.54
SPI_SCK2: J3.57, U5.54
SPI_SCK3: J4.57, U7.54
SPI_SCK4: J5.57, U9.54
SPI_SCK5: J6.57, U11.54
SPI_SCK6: J7.57, U13.54
SPI_SCK7: J8.57, U15.54
SPI_SCK8: J9.57, U17.54
SPI_SCK9: J10.57, U19.54
SPI_SCK10: J11.57, U21.54
SPI_SCK11: J12.57, U23.54
SPI_SCK12: J13.57, U25.54
SPI_SCK13: J14.57, U27.54
SPI_SCK14: J15.57, U29.54
SPI_SCK15: J16.57, U31.54
STAT: R3.2, U1.1
STAT1: R6.2, U3.1
STAT2: R9.2, U5.1
STAT3: R12.2, U7.1
STAT4: R15.2, U9.1
STAT5: R18.2, U11.1
STAT6: R21.2, U13.1
STAT7: R24.2, U15.1
STAT8: R27.2, U17.1
STAT9: R30.2, U19.1
STAT10: R33.2, U21.1
STAT11: R36.2, U23.1
STAT12: R39.2, U25.1
STAT13: R42.2, U27.1
STAT14: R45.2, U29.1
STAT15: R48.2, U31.1
SWDCK: J1.21, U1.26
SWDCK1: J2.21, U3.26
SWDCK2: J3.21, U5.26
SWDCK3: J4.21, U7.26
SWDCK4: J5.21, U9.26
SWDCK5: J6.21, U11.26
SWDCK6: J7.21, U13.26
SWDCK7: J8.21, U15.26
SWDCK8: J9.21, U17.26
SWDCK9: J10.21, U19.26
SWDCK10: J11.21, U21.26
SWDCK11: J12.21, U23.26
SWDCK12: J13.21, U25.26
SWDCK13: J14.21, U27.26
SWDCK14: J15.21, U29.26
SWDCK15: J16.21, U31.26
SWDIO: J1.23, U1.25
SWDIO1: J2.23, U3.25
SWDIO2: J3.23, U5.25
SWDIO3: J4.23, U7.25
SWDIO4: J5.23, U9.25
SWDIO5: J6.23, U11.25
SWDIO6: J7.23, U13.25
SWDIO7: J8.23, U15.25
SWDIO8: J9.23, U17.25
SWDIO9: J10.23, U19.25
SWDIO10: J11.23, U21.25
SWDIO11: J12.23, U23.25
SWDIO12: J13.23, U25.25
SWDIO13: J14.23, U27.25
SWDIO14: J15.23, U29.25
SWDIO15: J16.23, U31.25
TIM1_BKIN: J1.10, U1.41
TIM1_BKIN1: J2.10, U3.41
TIM1_BKIN2: J3.10, U5.41
TIM1_BKIN3: J4.10, U7.41
TIM1_BKIN4: J5.10, U9.41
TIM1_BKIN5: J6.10, U11.41
TIM1_BKIN6: J7.10, U13.41
TIM1_BKIN7: J8.10, U15.41
TIM1_BKIN8: J9.10, U17.41
TIM1_BKIN9: J10.10, U19.41
TIM1_BKIN10: J11.10, U21.41
TIM1_BKIN11: J12.10, U23.41
TIM1_BKIN12: J13.10, U25.41
TIM1_BKIN13: J14.10, U27.41
TIM1_BKIN14: J15.10, U29.41
TIM1_BKIN15: J16.10, U31.41
TIM1_ETR: J1.18, U1.79
TIM1_ETR1: J2.18, U3.79
TIM1_ETR2: J3.18, U5.79
TIM1_ETR3: J4.18, U7.79
TIM1_ETR4: J5.18, U9.79
TIM1_ETR5: J6.18, U11.79
TIM1_ETR6: J7.18, U13.79
TIM1_ETR7: J8.18, U15.79
TIM1_ETR8: J9.18, U17.79
TIM1_ETR9: J10.18, U19.79
TIM1_ETR10: J11.18, U21.79
TIM1_ETR11: J12.18, U23.79
TIM1_ETR12: J13.18, U25.79
TIM1_ETR13: J14.18, U27.79
TIM1_ETR14: J15.18, U29.79
TIM1_ETR15: J16.18, U31.79
TX1/DEV_RX1: J1.17, U1.51
TX1/DEV_RX2: J2.17, U3.51
TX1/DEV_RX3: J3.17, U5.51
TX1/DEV_RX4: J4.17, U7.51
TX1/DEV_RX5: J5.17, U9.51
TX1/DEV_RX6: J6.17, U11.51
TX1/DEV_RX7: J7.17, U13.51
TX1/DEV_RX8: J8.17, U15.51
TX1/DEV_RX9: J9.17, U17.51
TX1/DEV_RX10: J10.17, U19.51
TX1/DEV_RX11: J11.17, U21.51
TX1/DEV_RX12: J12.17, U23.51
TX1/DEV_RX13: J13.17, U25.51
TX1/DEV_RX14: J14.17, U27.51
TX1/DEV_RX15: J15.17, U29.51
TX1/DEV_RX16: J16.17, U31.51
UART_CTS: J1.15, U1.20
UART_CTS1: J2.15, U3.20
UART_CTS2: J3.15, U5.20
UART_CTS3: J4.15, U7.20
UART_CTS4: J5.15, U9.20
UART_CTS5: J6.15, U11.20
UART_CTS6: J7.15, U13.20
UART_CTS7: J8.15, U15.20
UART_CTS8: J9.15, U17.20
UART_CTS9: J10.15, U19.20
UART_CTS10: J11.15, U21.20
UART_CTS11: J12.15, U23.20
UART_CTS12: J13.15, U25.20
UART_CTS13: J14.15, U27.20
UART_CTS14: J15.15, U29.20
UART_CTS15: J16.15, U31.20
UART_RTS_DE: J1.13, U1.21
UART_RTS_DE1: J2.13, U3.21
UART_RTS_DE2: J3.13, U5.21
UART_RTS_DE3: J4.13, U7.21
UART_RTS_DE4: J5.13, U9.21
UART_RTS_DE5: J6.13, U11.21
UART_RTS_DE6: J7.13, U13.21
UART_RTS_DE7: J8.13, U15.21
UART_RTS_DE8: J9.13, U17.21
UART_RTS_DE9: J10.13, U19.21
UART_RTS_DE10: J11.13, U21.21
UART_RTS_DE11: J12.13, U23.21
UART_RTS_DE12: J13.13, U25.21
UART_RTS_DE13: J14.13, U27.21
UART_RTS_DE14: J15.13, U29.21
UART_RTS_DE15: J16.13, U31.21
USBIN_N: D3.4, J1.5
USBIN_N1: D6.4, J2.5
USBIN_N2: D9.4, J3.5
USBIN_N3: D12.4, J4.5
USBIN_N4: D15.4, J5.5
USBIN_N5: D18.4, J6.5
USBIN_N6: D21.4, J7.5
USBIN_N7: D24.4, J8.5
USBIN_N8: D27.4, J9.5
USBIN_N9: D30.4, J10.5
USBIN_N10: D33.4, J11.5
USBIN_N11: D36.4, J12.5
USBIN_N12: D39.4, J13.5
USBIN_N13: D42.4, J14.5
USBIN_N14: D45.4, J15.5
USBIN_N15: D48.4, J16.5
USBIN_P: D3.6, J1.3
USBIN_P1: D6.6, J2.3
USBIN_P2: D9.6, J3.3
USBIN_P3: D12.6, J4.3
USBIN_P4: D15.6, J5.3
USBIN_P5: D18.6, J6.3
USBIN_P6: D21.6, J7.3
USBIN_P7: D24.6, J8.3
USBIN_P8: D27.6, J9.3
USBIN_P9: D30.6, J10.3
USBIN_P10: D33.6, J11.3
USBIN_P11: D36.6, J12.3
USBIN_P12: D39.6, J13.3
USBIN_P13: D42.6, J14.3
USBIN_P14: D45.6, J15.3
USBIN_P15: D48.6, J16.3
USB_N: D3.3, U1.30
USB_N1: D6.3, U3.30
USB_N2: D9.3, U5.30
USB_N3: D12.3, U7.30
USB_N4: D15.3, U9.30
USB_N5: D18.3, U11.30
USB_N6: D21.3, U13.30
USB_N7: D24.3, U15.30
USB_N8: D27.3, U17.30
USB_N9: D30.3, U19.30
USB_N10: D33.3, U21.30
USB_N11: D36.3, U23.30
USB_N12: D39.3, U25.30
USB_N13: D42.3, U27.30
USB_N14: D45.3, U29.30
USB_N15: D48.3, U31.30
USB_P: D3.1, U1.29
USB_P1: D6.1, U3.29
USB_P2: D9.1, U5.29
USB_P3: D12.1, U7.29
USB_P4: D15.1, U9.29
USB_P5: D18.1, U11.29
USB_P6: D21.1, U13.29
USB_P7: D24.1, U15.29
USB_P8: D27.1, U17.29
USB_P9: D30.1, U19.29
USB_P10: D33.1, U21.29
USB_P11: D36.1, U23.29
USB_P12: D39.1, U25.29
USB_P13: D42.1, U27.29
USB_P14: D45.1, U29.29
USB_P15: D48.1, U31.29
V_BATT: D1.C, J1.72, U1.15
V_BATT1: D4.C, J2.72, U3.15
V_BATT2: D7.C, J3.72, U5.15
V_BATT3: D10.C, J4.72, U7.15
V_BATT4: D13.C, J5.72, U9.15
V_BATT5: D16.C, J6.72, U11.15
V_BATT6: D19.C, J7.72, U13.15
V_BATT7: D22.C, J8.72, U15.15
V_BATT8: D25.C, J9.72, U17.15
V_BATT9: D28.C, J10.72, U19.15
V_BATT10: D31.C, J11.72, U21.15
V_BATT11: D34.C, J12.72, U23.15
V_BATT12: D37.C, J13.72, U25.15
V_BATT13: D40.C, J14.72, U27.15
V_BATT14: D43.C, J15.72, U29.15
V_BATT15: D46.C, J16.72, U31.15

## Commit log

2022-12-13 Template cleanup, added datasheets and RM.
2022-12-14 Added schematic/board/initial library.
2023-01-09 Nearing layout completion.
2023-01-10 Layout complete.
2023-01-10 Last update for protos.
2023-01-17 Updates from Design Review v01
    Fix footprint.
    Reposition bottom silk
    Removed extraneous vias.
    Renamed some nets to match micromod connector.
    Rerouted some traces.
    Added ground vias near fast switching vias.
2023-01-17 Protos commit
    Schematic - Revector all fonts
    Board - Straighten one trace.
    Panel - Panelize and CAM.
2023-02-15 Move Gerbers to Production folder
2023-04-21 Update for v10
    Changelog from v01:
    * Connect unused GPIO to ground
    ** AN4899
    ** Reduces power consumption and noise
    * Add ESD to USB data lines
    ** This module is sensitive to it
2023-05-22 v10 Update
2023-05-22 Added examples.
2023-05-22 Added helpful documentation
2023-06-12 Update README.md
    Update README from SFE template with product info and photo.
